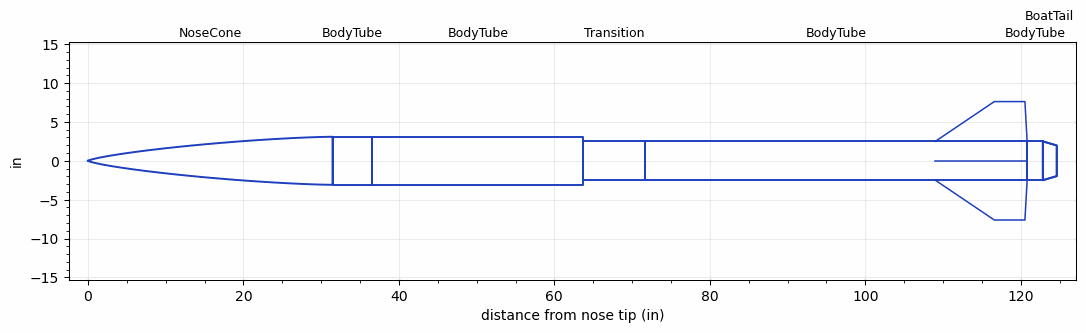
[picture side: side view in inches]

<RASAeroDocument>
 <FileVersion>2</FileVersion>
 <RocketDesign>
  <NoseCone>
   <Length>31.458</Length>
   <Diameter>6.18</Diameter>
   <Shape>Von Karman Ogive</Shape>
   <Location>0</Location>
  </NoseCone>
  <BodyTube>
   <Length>5.118</Length>
   <Diameter>6.18</Diameter>
   <Location>31.458</Location>
  </BodyTube>
  <BodyTube>
   <Length>27.165</Length>
   <Diameter>6.18</Diameter>
   <Location>36.576</Location>
  </BodyTube>
  <Transition>
   <Length>7.874</Length>
   <Diameter>5</Diameter>
   <Location>63.741</Location>
   <RearDiameter>5</RearDiameter>
  </Transition>
  <BodyTube>
   <Length>49.2126</Length>
   <Diameter>5</Diameter>
   <RailGuideDiameter>0.621</RailGuideDiameter>
   <RailGuideHeight>0.44</RailGuideHeight>
   <Location>71.615</Location>
   <Fin>
    <Count>4</Count>
    <Chord>11.811</Chord>
    <Span>5.1181</Span>
    <SweepDistance>7.5879</SweepDistance>
    <TipChord>3.937</TipChord>
    <Thickness>0.2362</Thickness>
    <LERadius>0.02</LERadius>
    <Location>11.811</Location>
    <AirfoilSection>Hexagonal</AirfoilSection>
    <FX1>1</FX1>
    <FX3>1</FX3>
   </Fin>
  </BodyTube>
  <BodyTube>
   <Length>2.022</Length>
   <Diameter>5</Diameter>
   <Location>120.8276</Location>
   <BoattailLength>1.791</BoattailLength>
   <BoattailRearDiameter>3.937</BoattailRearDiameter>
  </BodyTube>
  <BoatTail>
   <Length>1.791</Length>
   <Diameter>5</Diameter>
   <RearDiameter>3.937</RearDiameter>
   <Location>122.8496</Location>
  </BoatTail>
  <Surface>Smooth (Zero Roughness)</Surface>
  <ModifiedBarrowman>True</ModifiedBarrowman>
  <Turbulence>True</Turbulence>
  <UseBooster1>False</UseBooster1>
  <UseBooster2>False</UseBooster2>
 </RocketDesign>
 <LaunchSite>
  <Altitude>4596</Altitude>
  <Pressure>25.28</Pressure>
  <RodAngle>4</RodAngle>
  <RodLength>18.7</RodLength>
  <Temperature>42.61</Temperature>
  <WindSpeed>8.95</WindSpeed>
 </LaunchSite>
 <Recovery>
  <Altitude1>1000</Altitude1>
  <Altitude2>1312</Altitude2>
  <DeviceType1>Parachute</DeviceType1>
  <DeviceType2>Parachute</DeviceType2>
  <Event1>True</Event1>
  <Event2>True</Event2>
  <Size1>36.394</Size1>
  <Size2>96</Size2>
  <EventType1>Apogee</EventType1>
  <EventType2>Altitude</EventType2>
  <CD1>0.97</CD1>
  <CD2>2.2</CD2>
 </Recovery>
 <SimulationList>
  <Simulation>
   <SustainerEngine>O5500X  (AT)</SustainerEngine>
   <SustainerLaunchWt>75.4</SustainerLaunchWt>
   <SustainerNozzleDiameter>2.6929</SustainerNozzleDiameter>
   <SustainerCG>76.18</SustainerCG>
   <SustainerIgnitionDelay>0</SustainerIgnitionDelay>
   <Booster1SeparationDelay>0</Booster1SeparationDelay>
   <Booster1IgnitionDelay>0</Booster1IgnitionDelay>
   <IncludeBooster1>False</IncludeBooster1>
   <Booster2Delay>0</Booster2Delay>
   <IncludeBooster2>False</IncludeBooster2>
   <TimetoApogee>39.19943</TimetoApogee>
   <MaxAltitude>29480.49</MaxAltitude>
   <MaxVelocity>2039.423</MaxVelocity>
  </Simulation>
 </SimulationList>
</RASAeroDocument>
